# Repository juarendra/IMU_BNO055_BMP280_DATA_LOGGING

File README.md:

# IMU_BNO055_BMP280_DATA_LOGGING

## Spesification
- ESP32 WROOM
- USB TYPE C
- FT231 as USB Proggrammer
- BNO055
- BMP280
- OLED DISPLAY
- I2C expander for Button
- Modul charger tp4056 for Charger Lipo Batt
- Switch On OFF
- SD Card as save Data Loging

## Preview Hardware
<p align="center">

</p>

## USAGE 
- First you need to order or print the PCB based the gerber file on [this folder](https://github.com/juarendra/IMU_BNO055_BMP280_DATA_LOGGING/tree/main/GERBER)
- there are two PCB File, first is the MAIN Board and second is the UI with OLED and Button
- you need to print all PCB file to your favorite Manufacture PCB.
- then you can order all component based the BOM LIST file on [this folder](https://github.com/juarendra/IMU_BNO055_BMP280_DATA_LOGGING/tree/main/BOM).
- after All PCBs and All Component are receive, you can start the assembly 
- Then Print Case on [this Folder](https://github.com/juarendra/IMU_BNO055_BMP280_DATA_LOGGING/tree/main/CASE) with your 3D print

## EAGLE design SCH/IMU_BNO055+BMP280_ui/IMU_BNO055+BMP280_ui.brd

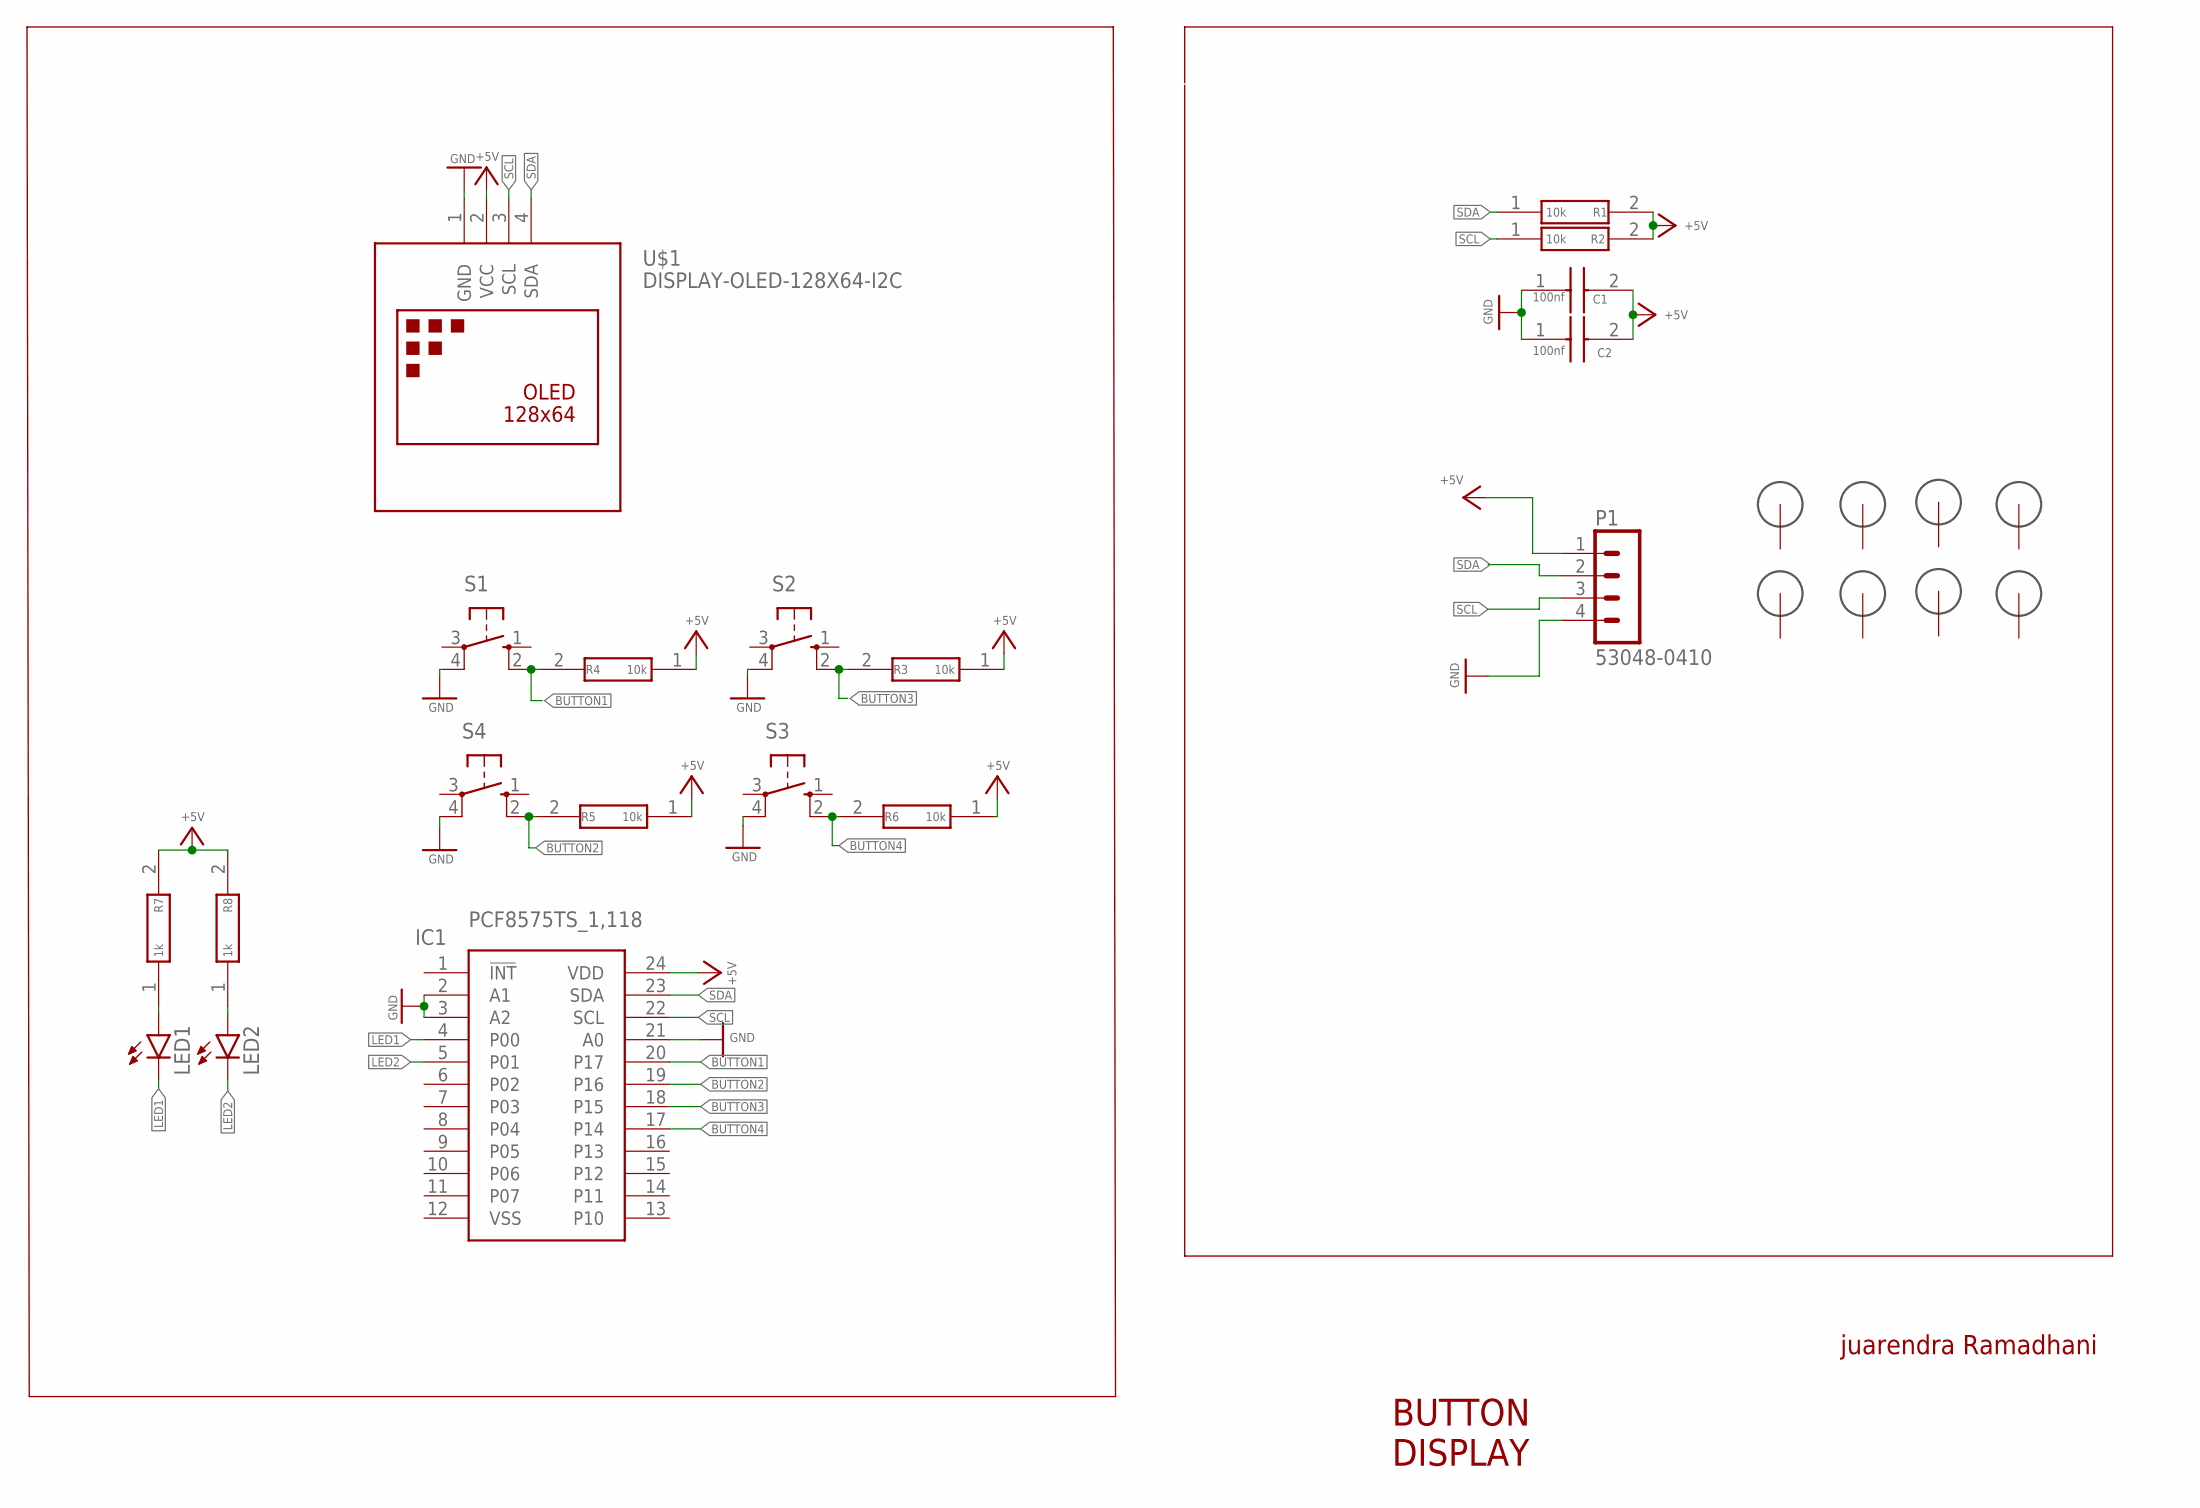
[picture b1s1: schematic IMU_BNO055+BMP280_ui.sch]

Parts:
C1, C2: 100nf; CAPC1608X87N
H1, H2, H3, H4, H5, H6, H7, H8: 3MM_HOLE
IC1: PCF8575TS_1,118; SOP65P775X200-24N
LED1, LED2: LED3MM
P1: 53048-0410
R1, R2, R3, R4, R5, R6: 10k; RESC1608X55N
R7, R8: 1k; RESC1608X55N
S1, S2, S3, S4: 10-XX; B3F-10XX
U$1: DISPLAY-OLED-128X64-I2C

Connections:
+5V: C1.2, C2.2, IC1.24 (VDD), P1.1, R1.2, R2.2, R3.1, R4.1, R5.1, R6.1, R7.2, R8.2, U$1.2 (VCC)
BUTTON1: IC1.20 (P17), R4.2, S1.2 (S1)
BUTTON2: IC1.19 (P16), R5.2, S4.2 (S1)
BUTTON3: IC1.18 (P15), R3.2, S2.2 (S1)
BUTTON4: IC1.17 (P14), R6.2, S3.2 (S1)
GND: C1.1, C2.1, IC1.2 (A1), IC1.3 (A2), IC1.21 (A0), P1.4, S1.4 (P1), S2.4 (P1), S3.4 (P1), S4.4 (P1), U$1.1 (GND)
LED1: IC1.4 (P00), LED1.K (C)
LED2: IC1.5 (P01), LED2.K (C)
unnamed: LED1.A, R7.1
unnamed: LED2.A, R8.1
SCL: IC1.22 (SCL), P1.3, R2.1, U$1.3 (SCL)
SDA: IC1.23 (SDA), P1.2, R1.1, U$1.4 (SDA)

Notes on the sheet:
BUTTON DISPLAY
juarendra Ramadhani

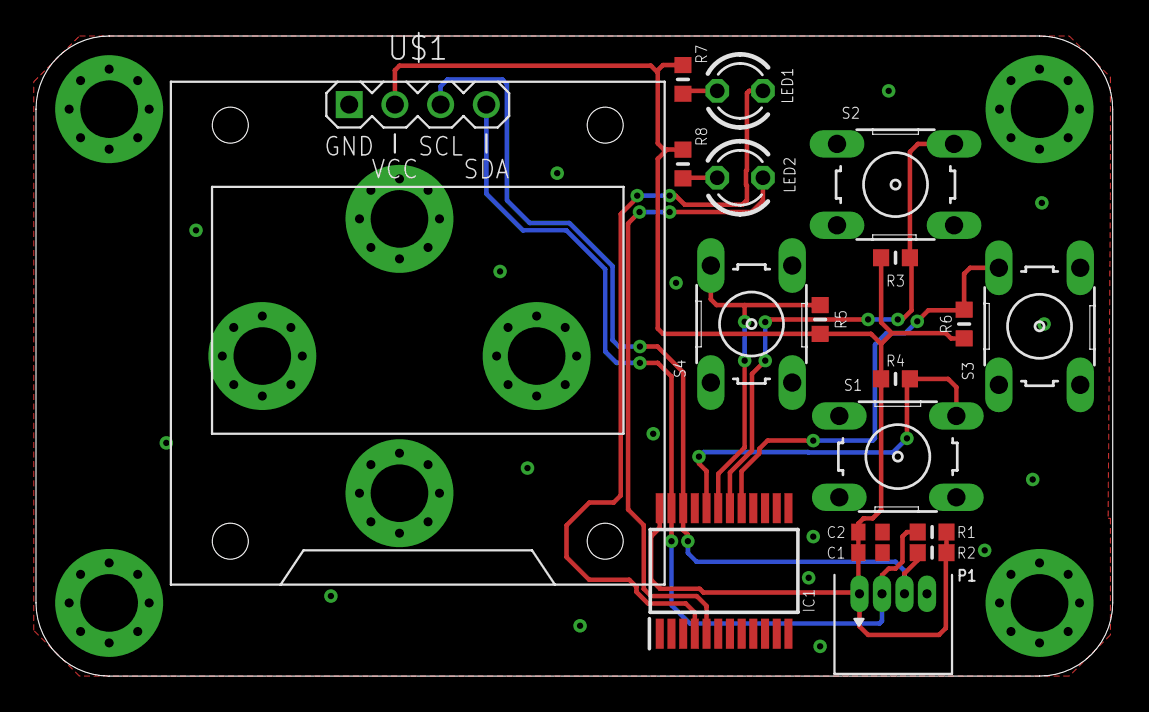
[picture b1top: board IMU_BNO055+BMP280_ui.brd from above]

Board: 2 copper layers, 59.8 x 35.6 mm, 27 parts (0 on the bottom side), 12 nets.

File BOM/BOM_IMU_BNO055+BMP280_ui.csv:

"Qty";"Value";"Device";"Package";"Parts";"Description";"AVAILABILITY";"CHECK_PRICES";"DESCRIPTION";"DIGIKEY_PARTNUMBER";"DIGIKEY_PRICE-STOCK";"HEIGHT";"MANUFACTURER_NAME";"MANUFACTURER_PART_NUMBER";"MF";"MOUSER_PART_NUMBER";"MOUSER_PRICE-STOCK";"MP";"MPN";"OC_FARNELL";"OC_NEWARK";"PACKAGE";"POPULARITY";"PRICE";"SNAPEDA_LINK";"VALUE";
"4";"";"10-XX";"B3F-10XX";"S1, S2, S3, S4";"OMRON SWITCH";"";"";"";"";"";"";"";"";"";"";"";"";"B3F-1000";"176432";"36M3542";"";"72";"";"";"";
"2";"";"LED3MM";"LED3MM";"LED1, LED2";"LED";"";"";"";"";"";"";"";"";"";"";"";"";"";"";"";"";"97";"";"";"";
"2";"100nf";"885012206071";"CAPC1608X87N";"C1, C2";"Wurth Elektronik 0603 WCAP-CSGP 100nF Ceramic Multilayer Capacitor, 25 V dc, +125C, X7R Dielectric, +/-10%";"";"";"Wurth Elektronik 0603 WCAP-CSGP 100nF Ceramic Multilayer Capacitor, 25 V dc, +125C, X7R Dielectric, +/-10%";"732-7989-1-ND";"https://www.digikey.com/product-detail/en/w%C3%BCrth-elektro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";"0.87mm";"Wurth Elektronik";"885012206071";"";"710-885012206071";"https://www.mouser.co.uk/ProductDetail/Wurth-Elektronik/8850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";"";"";"";"";"";"";"";"";"100nf";
"6";"10k";"ESR03EZPJ103";"RESC1608X55N";"R1, R2, R3, R4, R5, R6";"Thick Film Resistors - SMD 0603 10Kohm 5% Anti Surge AEC-Q200";"";"";"Thick Film Resistors - SMD 0603 10Kohm 5% Anti Surge AEC-Q200";"RHM10KDCT-ND";"https://www.digikey.com/product-detail/en/rohm-semiconductor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";"0.55mm";"ROHM Semiconductor";"ESR03EZPJ103";"";"755-ESR03EZPJ103";"https://www.mouser.com/Search/Refine.aspx?Keyword=755-ESR03EZPJ103";"";"";"";"";"";"";"";"";"10k";
"2";"1k";"ESR03EZPJ102";"RESC1608X55N";"R7, R8";"Thick Film Resistors - SMD 0603 1Kohm 5% Anti Surge AEC-Q200";"";"";"Thick Film Resistors - SMD 0603 1Kohm 5% Anti Surge AEC-Q200";"RHM1.0KDCT-ND";"https://www.digikey.com/product-detail/en/rohm-semiconductor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";"0.55mm";"ROHM Semiconductor";"ESR03EZPJ102";"";"755-ESR03EZPJ102";"https://www.mouser.co.uk/ProductDetail/ROHM-Semiconductor/ES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";"";"";"";"";"";"";"";"";"1k";
"8";"3MM_HOLE";"3MM_HOLE";"3MM_HOLE";"H1, H2, H3, H4, H5, H6, H7, H8";"Cool looking 3mm hole with ground connection";"";"";"";"";"";"";"";"";"";"";"";"";"";"";"";"";"";"";"";"";
"1";"53048-0410";"53048-0410";"53048-0410";"P1";"HEADER  Check availability";"In Stock";"https://www.snapeda.com/parts/53048-0410/Molex/view-part/?ref=eda";" 4 way through board PCB 90deg header | Molex Incorporated 53048-0410 ";"";"";"";"";"";"Molex";"";"";"53048-0410";"";"";"";"None";"";"None";"https://www.snapeda.com/parts/53048-0410/Molex/view-part/?ref=snap";"";
"1";"DISPLAY-OLED-128X64-I2C";"DISPLAY-OLED-128X64-I2C";"DISPLAY-OLED-128X64-I2C";"U$1";"128x64 Dot Matrix OLED Module based on SSD1306 chip";"";"";"";"";"";"";"";"";"";"";"";"";"";"";"";"";"";"";"";"";
"1";"PCF8575TS_1,118";"PCF8575TS_1,118";"SOP65P775X200-24N";"IC1";"Interface - I/O Expanders";"";"";"Interface - I/O Expanders";"";"";"2mm";"NXP";"PCF8575TS/1,118";"";"771-PCF8575TSDB-T";"https://www.mouser.co.uk/ProductDetail/NXP-Semiconductors/PC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";"";"";"";"";"";"";"";"";"";

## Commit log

2024-04-30 FEAT: add Schematic and Gerber File
2024-04-30 FEAT: add BOM :IST
2024-04-30 FEAT: update doc
2024-04-30 FEAT: Add Case
2024-05-31 FIX: fix ic stepdown to 3v3
2024-05-31 FIX: BOM LIST based from change ic stepdown

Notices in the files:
parts and their libraries:
diy-modules: Released under the Creative Commons Attribution 4.0 International License: http://creativecommons.org/licenses/by/4.0
